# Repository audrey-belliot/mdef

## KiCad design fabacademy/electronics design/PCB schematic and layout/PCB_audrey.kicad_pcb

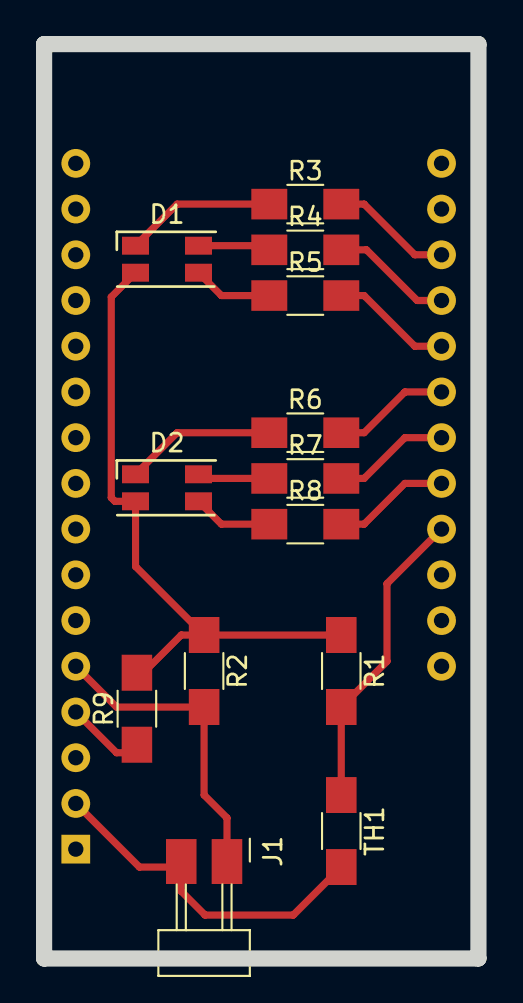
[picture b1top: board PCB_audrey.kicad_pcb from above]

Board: 2 copper layers, 24.1 x 50.8 mm, 14 parts (1 on the bottom side), 16 nets.

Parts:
A1: Adafruit_Feather_HUZZAH32_ESP32; Adafruit_Feather
D1, D2: LED_RGB_CLV1A-FKB; LED_RGB_Cree_CLV1A-FKB_3.2x2.8mm
J1: Conn_Header_JST_PH_1x02_P2mm_Vertical_SMD; PinHeader_1x02_P2.54mm_Horizontal_SMD
R1, R2, R3, R4, R5, R6, R7, R8, R9: R; R_1206
TH1: Thermistor_NTC; R_1206

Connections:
Blue1: A1.21, R5.2
Blue2: A1.24, R8.2
GND: A1.4, D1.2, D2.2, R1.1, R2.1, R9.1, R9.2
Green1: A1.20, R4.2
Green2: A1.23, R7.2
unnamed: D1.1, R3.1
unnamed: D1.3, R5.1
unnamed: D1.4, R4.1
unnamed: D2.1, R6.1
unnamed: D2.3, R8.1
unnamed: D2.4, R7.1
Red1: A1.19, R3.2
Red2: A1.22, R6.2
VCC: A1.2, J1.2, TH1.2
VoltageDiv1: A1.25, R1.2, TH1.1
VoltageDiv2: A1.5, J1.1, R2.2

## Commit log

2021-10-07 deploy: 3f485593245c9622cf53b14ca743f2ce14824423
2021-10-08 deploy: 54ee7829fcea82d450816f7f91ba80981bbd2040
2021-10-08 text bootcamp
2021-10-08 deploy: e00a923c41d7fe6e41c1c929b6c29e281c3748b4
2021-10-08 Change name in header
2021-10-08 deploy: cfd05861ed3c684b465b23fc3ac3bac2453c9d11
2021-10-08 Rename header
2021-10-08 deploy: 1f6efecfddd27722d61961a1575ab88588ea5c15
2021-10-09 add folder in repo
2021-10-09 deploy: 3b23fc1a31629c2452c2f27544e603c8991625eb
2021-10-09 Replace MDEF template by custom page
2021-10-09 Deplace index file
2021-10-09 Change text in first page
2021-10-09 First page style tests
2021-10-10 test with new workflow
2021-10-10 Style website
2021-10-10 Rename Week1.html to week1.html
2021-10-10 Additional text updates
2021-10-12 Updates html home and week
2021-10-12 Embed miro boards with skills
2021-10-13 Text and imagies week 1
2021-10-18 New page for week 2
2021-10-30 week3
2021-11-01 week 4 post
2021-11-01 image update week4
2021-11-03 week5 day 1
2021-11-07 week 5 24h experiment
2021-11-07 add agri empty page
2021-11-08 bio agro reflections
2021-11-14 week 6 assigments
2021-11-15 Bio agri zero article synopsis
2021-11-15 link to article agri
2021-11-18 igem agro
2021-11-18 update text agri link name
2021-11-22 documentation
2021-11-22 agri reflections images
2021-11-25 documentation process
2021-11-26 tech reflections
2021-11-29 community engagement
2021-11-29 link miro
2021-12-19 extended intelligences reflections
2021-12-19 seminar page update
2021-12-24 design dialogues
2021-12-24 seminar page
2022-01-17 term2 week1
2022-01-24 design studio 2 kickoff
2022-01-30 fabacademy page
2022-01-31 image fab week1
2022-01-31 fab w1
2022-02-02 page titles
2022-02-02 typo w1
2022-02-06 Remixing material reflection
2022-02-08 design studio 1PP
2022-02-08 image design intervention
2022-02-08 FABACADEMY WEEK 2
2022-02-09 modif fab week2 text
2022-02-20 remixing materials 2
2022-02-22 links to interventions
2022-02-23 eco images remixing materials
2022-02-23 carbon page 15
2022-02-23 carbon label
2022-02-23 fab weekly task laser
2022-02-23 fab challenge 1
2022-02-25 update challenge page
2022-03-06 fab week 4
2022-03-08 design studio 3
2022-03-08 typo
2022-03-10 fab challenge 3D print
2022-03-14 about page
2022-03-18 Making sense
2022-03-18 impact sense making
2022-03-30 fab week 6 electronic design
2022-04-14 challenge 2
2022-04-17 aows2
2022-04-19 weekly task fab CNC
2022-04-25 future talks
2022-05-01 term 3
2022-05-01 ds2-1 update
2022-05-09 fab academy week7
2022-05-16 Fab Academy Tasks
2022-05-16 update tools
2022-05-16 size column
2022-05-22 DESIGN STUDIO 3 2
2022-05-29 design ethics
2022-06-05 challenge 4
2022-06-06 challenge3 post
2022-06-06 TASKS
2022-06-06 MENU
2022-06-06 files
2022-06-06 molding
2022-06-08 fab17
2022-06-10 fab 18
2022-06-13 tech track
2022-06-14 fab task 15
2022-06-14 about
2022-06-16 weeknumber
2022-06-17 reflection 3
